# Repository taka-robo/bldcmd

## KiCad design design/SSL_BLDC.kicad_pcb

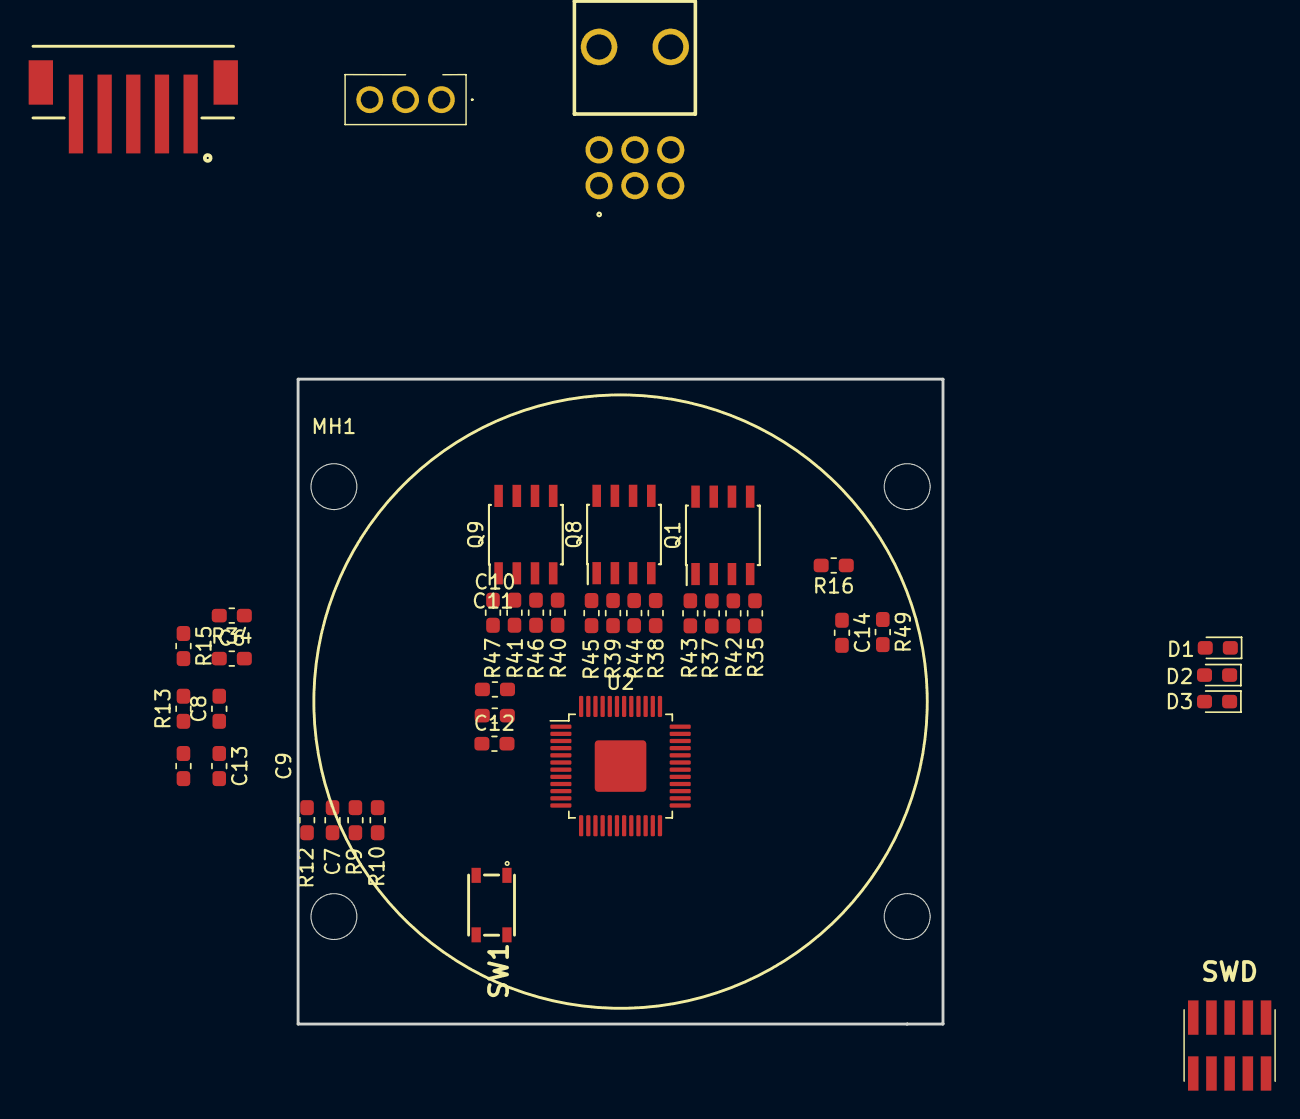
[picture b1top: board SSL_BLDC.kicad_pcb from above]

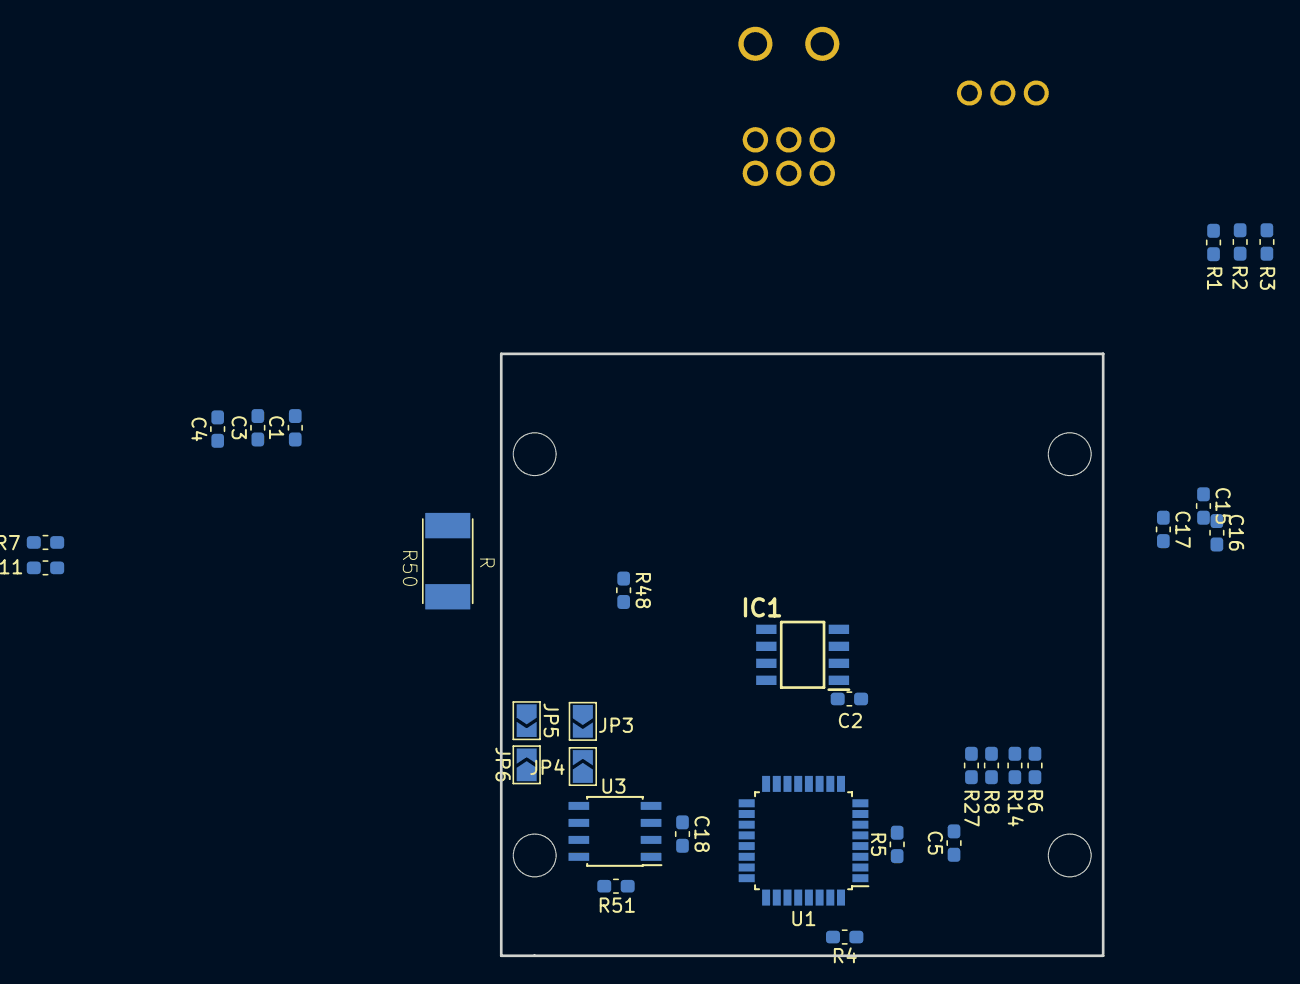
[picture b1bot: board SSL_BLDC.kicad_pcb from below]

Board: 2 copper layers, 45.0 x 45.0 mm, 75 parts (30 on the bottom side), 64 nets, no tracks yet.

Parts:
C1, C3, C4: 1n; C_0603_1608Metric_Pad1.05x0.95mm_HandSolder
C2: 0.1; C_0603_1608Metric_Pad1.05x0.95mm_HandSolder
C5: C_Small; C_0603_1608Metric_Pad1.05x0.95mm_HandSolder
C6, C13, C18: 0.1u; C_0603_1608Metric_Pad1.05x0.95mm_HandSolder
C7: 0.68u; C_0603_1608Metric_Pad1.05x0.95mm_HandSolder
C8: 0.47u; C_0603_1608Metric_Pad1.05x0.95mm_HandSolder
C9: 10u; C_0603_1608Metric_Pad1.05x0.95mm_HandSolder
C10, C11, C12: 0.22u; C_0603_1608Metric_Pad1.05x0.95mm_HandSolder
C14: 1nF; C_0603_1608Metric_Pad1.05x0.95mm_HandSolder
C15, C16, C17: 220u; C_0603_1608Metric_Pad1.05x0.95mm_HandSolder
D1, D2, D3: BLUE; LED_0603_1608Metric_Pad1.05x0.95mm_HandSolder
IC1: AS5601-ASOM; SOIC127P600X175-8N
J1: HallIn/PH5; B5B-PH-SM4-TB
J2: INPUT/nanofit6; 105314-1206
J5: motor/nanofit3; 1053091203
JP3: DIR; SolderJumper-2_P1.3mm_Open_TrianglePad1.0x1.5mm
JP4: CANL; SolderJumper-2_P1.3mm_Open_TrianglePad1.0x1.5mm
JP5: PWM; SolderJumper-2_P1.3mm_Open_TrianglePad1.0x1.5mm
JP6: CANH; SolderJumper-2_P1.3mm_Open_TrianglePad1.0x1.5mm
MH1, MH2, MH3, MH4: M3; MountingHole_3.2mm_M3
Q1, Q8, Q9: IRF8313TRPBF; SOIC-8_3.9x4.9mm_P1.27mm
R1, R2, R3, R48, R49: 1k; R_0603_1608Metric_Pad1.05x0.95mm_HandSolder
R4, R5, R42, R43, R44, R45, R46, R47: 470k; R_0603_1608Metric_Pad1.05x0.95mm_HandSolder
R6, R7, R8, R11, R14, R16, R27: 10k; R_0603_1608Metric_Pad1.05x0.95mm_HandSolder
R9: 56k; R_0603_1608Metric_Pad1.05x0.95mm_HandSolder
R10: RDEAD; R_0603_1608Metric_Pad1.05x0.95mm_HandSolder
R12, R13, R34: 100k; R_0603_1608Metric_Pad1.05x0.95mm_HandSolder
R15: 27k; R_0603_1608Metric_Pad1.05x0.95mm_HandSolder
R35, R37, R38, R39, R40, R41: 10; R_0603_1608Metric_Pad1.05x0.95mm_HandSolder
R50: R; RESC6331X70N
R51: 0; R_0603_1608Metric_Pad1.05x0.95mm_HandSolder
SW1: SW_Push_Dual; SMT(4.2X3.2)
SWD: SWD; M503600542R
U1: STM32F303K8Tx; LQFP-32_7x7mm_P0.8mm
U2: A3930_1; LQFP-48-1EP_7x7mm_P0.5mm_EP3.6x3.6mm
U3: SN65HVD230; SOIC-8_3.9x4.9mm_P1.27mm

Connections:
+3V3: C2.1, C18.1, IC1.1, IC1.2, J2.2, R5.2, R16.2, U1.1, U1.5, U1.17, U3.3
+5V: C6.1, J1.1, R6.2, R8.2, R11.2, R12.2, R13.2, R34.2, U2.3, U2.4
+BATT: C15.1, C16.1, C17.1, J2.1, Q1.5, Q1.6, Q8.5, Q8.6, Q9.5, Q9.6, R7.2, R15.1, U2.24, U2.45
/drive/BRAKE: R13.1, U2.8
/drive/COAST: R34.1, U2.46
/drive/CSN: C14.1, R48.2, U2.21
/drive/CSP: C14.2, R49.2, U2.22
/drive/GHA: R40.2, U2.32
/drive/GHB: R38.2, U2.29
/drive/GHC: R35.2, U2.26
/drive/GLA: R41.2, U2.36
/drive/GLB: R39.2, U2.35
/drive/GLC: R37.2, U2.34
/drive/LSS: C13.2, C15.2, C16.2, C17.2, Q1.1, Q8.1, Q9.1, R43.2, R45.2, R47.2, R48.1, R50.1, U2.38
/drive/MODE: R12.1, U2.15
CANH: JP6.1, U3.7
CANL: JP4.1, U3.6
CAN_RX: U1.21, U3.1
CAN_TX: U1.22, U3.4
CSOUT: U1.6, U2.19
DIR: JP3.1, U1.12, U2.9
ESF: U1.15, U2.39
FF1: U1.13, U2.6
FF2: U1.14, U2.5
GND: C1.2, C2.2, C3.2, C4.2, C5.2, C6.2, C7.2, C9.1, C13.1, C18.2, D1.1, D2.1, D3.1, IC1.4, J1.5, J2.5, J2.6, R4.1, R9.2, R10.2, R14.2, R27.2, R49.1, R50.2, R51.2, SW1.1, SW1.3, SWD.3, SWD.5, U1.16, U1.32, U2.17, U2.41, U3.2
H1: C1.1, R3.2, U2.10
H2: C3.1, R2.2, U2.11
H3: C4.1, R1.2, U2.12
I2C1_SCL: IC1.7, U1.25
I2C1_SDA: IC1.6, U1.30
unnamed: C7.1, R9.1, U2.16
unnamed: C8.1, U2.43
unnamed: C8.2, U2.42
unnamed: C9.2, U2.40
unnamed: C10.1, U2.33
unnamed: C11.1, U2.30
unnamed: C12.1, U2.27
unnamed: D1.2, R7.1
unnamed: D2.2, R11.1
unnamed: D3.2, R16.1
unnamed: J1.2, R1.1
unnamed: J1.3, R2.1
unnamed: J1.4, R3.1
unnamed: J2.3, JP5.2, JP6.2
unnamed: J2.4, JP3.2, JP4.2
unnamed: Q1.2, R37.1, R43.1
unnamed: Q1.4, R35.1, R42.1
unnamed: Q8.2, R39.1, R45.1
unnamed: Q8.4, R38.1, R44.1
unnamed: Q9.2, R41.1, R47.1
unnamed: Q9.4, R40.1, R46.1
unnamed: R4.2, U1.31
unnamed: R10.1, U2.18
unnamed: R6.1, R14.1, U2.20
unnamed: R15.2, U2.2
unnamed: R8.1, R27.1, U2.23
unnamed: R51.1, U3.8
PWM: JP5.1, U1.11, U2.14
RESET: C5.1, R5.1, SW1.2, SW1.4, SWD.10, U1.4
SWCLK: SWD.4, U1.24
SWDIO: SWD.2, U1.23
phase_A: C10.2, J5.3, Q9.3, Q9.7, Q9.8, R46.2, U2.31
phase_B: C11.2, J5.2, Q8.3, Q8.7, Q8.8, R44.2, U2.28
phase_C: C12.2, J5.1, Q1.3, Q1.7, Q1.8, R42.2, U2.25

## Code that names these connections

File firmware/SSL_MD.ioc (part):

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Mcu.Name=STM32F303K(6-8)Tx
Mcu.Package=LQFP32
Mcu.UserName=STM32F303K8Tx
PA0.Mode=IN1-Single-Ended
PA0.Signal=ADC1_IN1
PA10.Mode=Asynchronous
PA10.Signal=USART1_RX
PA11.Mode=Master
PA11.Signal=CAN_RX
PA12.Mode=Master
PA12.Signal=CAN_TX
PA13.Mode=Serial_Wire
PA13.Signal=SYS_JTMS-SWDIO
PA14.Mode=Serial_Wire
PA14.Signal=SYS_JTCK-SWCLK
PA15.Mode=I2C
PA15.Signal=I2C1_SCL
PA5.Signal=S_TIM2_CH1_ETR
PA6.Signal=GPIO_Output
PA7.Signal=GPIO_Input
PA9.Mode=Asynchronous
PA9.Signal=USART1_TX
PB0.Signal=GPIO_Input
PB1.Signal=GPIO_Input
PB7.Mode=I2C
PB7.Signal=I2C1_SDA
RCC.HSEPLLFreq_Value=8000000
RCC.HSE_VALUE=8000000
RCC.SYSCLKFreq_VALUE=8000000
board=custom
